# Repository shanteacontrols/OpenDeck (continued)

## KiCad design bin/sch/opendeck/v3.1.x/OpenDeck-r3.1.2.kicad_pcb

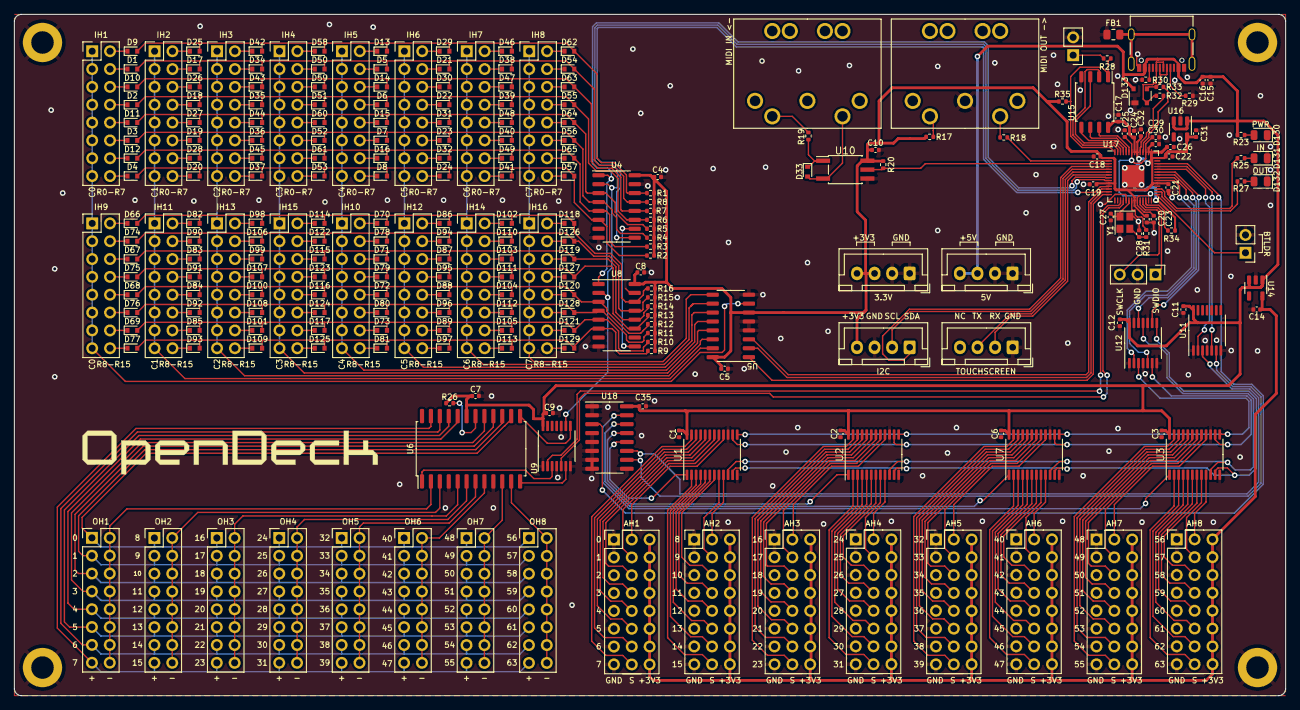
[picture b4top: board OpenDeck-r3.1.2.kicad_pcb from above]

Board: 2 copper layers, 181.0 x 97.0 mm, 262 parts (0 on the bottom side), 304 nets.

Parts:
AH1, AH2, AH3, AH4, AH5, AH6, AH7, AH8: 3x08
C1, C2, C3, C4, C5, C6, C7, C8, C9, C10, C11, C12, C16, C17, C18, C19, C20, C21, C22, C23, C24, C25, C26, C32, C35: 100n; C_0402_1005Metric
C14, C29, C30, C31: 1u; C_0402_1005Metric
C15: 10u; C_0402_1005Metric
C27, C28: 16p; C_0402_1005Metric
D1, D2, D3, D4, D5, D6, D7, D8, D9, D10, D11, D12, D13, D14, D15, D16, D17, D18, D19, D20, D21, D22, D23, D24, D25, D26, D27, D28, D29, D30, D31, D32, D33, D34, D35, D36, D37, D38, D39, D40, D41, D42, D43, D44, D45, D46, D47, D48, D49, D50, D51, D52, D53, D54, D55, D56, D57, D58, D59, D60, D61, D62, D63, D64, D65, D66, D67, D68, D69, D70, D71, D72, D73, D74, D75, D76, D77, D78, D79, D80, D81, D82, D83, D84, D85, D86, D87, D88, D89, D90, D91, D92, D93, D94, D95, D96, D97, D98, D99, D100, D101, D102, D103, D104, D105, D106, D107, D108, D109, D110, D111, D112, D113, D114, D115, D116, D117, D118, D119, D120, D121, D122, D123, D124, D125, D126, D127, D128, D129: 1N4148WT; D_SOD-523
D130: Red; LED_0805_2012Metric
D131: Green; LED_0805_2012Metric
D132: Blue; LED_0805_2012Metric
D133: PRTR5V0U2X; SOT-143
FB1: FerriteBead; R_0805_2012Metric
H1, H2, H3, H4: MountingHole_Pad; MountingHole_3.2mm_M3_DIN965_Pad
IH1, IH2, IH3, IH4, IH5, IH6, IH7, IH8, IH9, IH10, IH11, IH12, IH13, IH14, IH15, IH16: Conn_02x08_Top_Bottom; PinHeader_2x08_P2.54mm_Vertical
J1, J2: DIN-5; DIN5
J3, J6, J7, J8: Conn_01x04; JST_XH_B4B-XH-A_1x04_P2.50mm_Vertical
J5, J11: Conn_01x02; PinHeader_1x02_P2.54mm_Vertical
J9: TYPE-C-31-M-12
J10: Conn_01x03; PinHeader_1x03_P2.54mm_Vertical
OH1, OH2, OH3, OH4, OH5, OH6, OH7, OH8: Conn_02x08_Top_Bottom; PinHeader_2x08_P2.54mm_Vertical
R1, R2, R3, R4, R5, R6, R7, R8, R9, R10, R11, R12, R13, R14, R15, R16, R20: 4.7k; R_0402_1005Metric
R17: 33; R_0402_1005Metric
R18: 10; R_0402_1005Metric
R19: 220; R_0402_1005Metric
R23, R27, R28, R31: 1k; R_0402_1005Metric
R25: 680; R_0402_1005Metric
R26, R34, R35: 10k; R_0402_1005Metric
R29, R30: 5.1k; R_0402_1005Metric
R32, R33: 27; R_0402_1005Metric
U1, U2, U3, U7: 74HC4067; TSSOP-24_4.4x7.8mm_P0.65mm
U4, U8: 74HC165; SO-16_3.9x9.9mm_P1.27mm
U5: 74HC138; SO-16_3.9x9.9mm_P1.27mm
U6: MAX7219; SOIC-24W_7.5x15.4mm_P1.27mm
U9, U11, U12: 74HCT125; TSSOP-14_4.4x5mm_P0.65mm
U10: TLP2362; SO-5_4.4x3.6mm_P1.27mm
U14, U16: SPX3819M5; SOT-23-5
U15: W25Q128JVS; SOIC-8_5.23x5.23mm_P1.27mm
U17: RP2040; QFN-56-1EP_7x7mm_P0.4mm_EP3.2x3.2mm
U18: 4051; SOIC-16_3.9x9.9mm_P1.27mm
Y1: 12MHz; Crystal_SMD_2520-4Pin_2.5x2.0mm

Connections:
+1V1: C23.2, C25.2, C29.2, U17.23 (DVDD), U17.45 (VREG_VOUT), U17.50 (DVDD)
+3.3VADC: AH1.17, AH1.18, AH1.19, AH1.20, AH1.21, AH1.22, AH1.23, AH1.24, AH2.17, AH2.18, AH2.19, AH2.20, AH2.21, AH2.22, AH2.23, AH2.24, AH3.17, AH3.18, AH3.19, AH3.20, AH3.21, AH3.22, AH3.23, AH3.24, AH4.17, AH4.18, AH4.19, AH4.20, AH4.21, AH4.22, AH4.23, AH4.24, AH5.17, AH5.18, AH5.19, AH5.20, AH5.21, AH5.22, AH5.23, AH5.24, AH6.17, AH6.18, AH6.19, AH6.20, AH6.21, AH6.22, AH6.23, AH6.24, AH7.17, AH7.18, AH7.19, AH7.20, AH7.21, AH7.22, AH7.23, AH7.24, AH8.17, AH8.18, AH8.19, AH8.20, AH8.21, AH8.22, AH8.23, AH8.24, C14.2, U14.5 (OUT)
+3V3: C4.2, C5.2, C8.2, C10.2, C17.1, C18.1, C19.1, C20.1, C21.1, C22.1, C24.1, C26.1, C30.1, C31.2, C32.1, J6.4, J7.3, J7.4, R1.2, R2.2, R3.2, R4.2, R5.2, R6.2, R7.2, R8.2, R9.2, R10.2, R11.2, R12.2, R13.2, R14.2, R15.2, R16.2, R17.2, R20.1, R34.1, R35.1, U4.16 (VCC), U5.6 (E3), U5.16 (VCC), U8.16 (VCC), U10.6 (VCC), U15.8 (VCC), U16.5 (OUT), U17.1 (IOVDD), U17.10 (IOVDD), U17.22 (IOVDD), U17.33 (IOVDD), U17.42 (IOVDD), U17.43 (ADC_AVDD), U17.44 (VREG_VIN), U17.48 (USB_VDD), U17.49 (IOVDD)
+5V: C1.2, C2.2, C3.2, C6.2, C7.2, C9.2, C11.2, C12.2, C15.2, C16.2, C35.2, D133.4 (VCC), J8.3, J8.4, J9.A4/B9 (VBUS), J9.B4/A9 (VBUS), R23.1, R26.1, U1.24 (VCC), U2.24 (VCC), U3.24 (VCC), U6.19 (V+), U7.24 (VCC), U9.14 (VCC), U11.14 (VCC), U12.14 (VCC), U14.1 (IN), U14.3 (EN), U16.1 (IN), U16.3 (EN), U18.16 (VCC)
/Analog/MUX_COMMON_1: U1.1 (COM), U18.12 (Y3)
/Analog/MUX_COMMON_2: U2.1 (COM), U18.13 (Y0)
/Analog/MUX_COMMON_3: U7.1 (COM), U18.14 (Y1)
/Analog/MUX_COMMON_4: U3.1 (COM), U18.15 (Y2)
/Analog/MUX_S0_5V: U1.10 (S0), U2.10 (S0), U3.10 (S0), U7.10 (S0), U12.11
/Analog/MUX_S1_5V: U1.11 (S1), U2.11 (S1), U3.11 (S1), U7.11 (S1), U12.8
/Analog/MUX_S2_5V: U1.14 (S2), U2.14 (S2), U3.14 (S2), U7.14 (S2), U12.6
/Analog/MUX_S3_5V: U1.13 (S3), U2.13 (S3), U3.13 (S3), U7.13 (S3), U12.3
/Analog/Multiplexer 1/A_IN_0: AH2.9, U1.9 (Y0)
/Analog/Multiplexer 1/A_IN_1: AH2.10, U1.8 (Y1)
/Analog/Multiplexer 1/A_IN_2: AH2.11, U1.7 (Y2)
/Analog/Multiplexer 1/A_IN_3: AH2.12, U1.6 (Y3)
/Analog/Multiplexer 1/A_IN_4: AH2.13, U1.5 (Y4)
/Analog/Multiplexer 1/A_IN_5: AH2.14, U1.4 (Y5)
/Analog/Multiplexer 1/A_IN_6: AH2.15, U1.3 (Y6)
/Analog/Multiplexer 1/A_IN_7: AH2.16, U1.2 (Y7)
/Analog/Multiplexer 1/A_IN_8: AH1.16, U1.23 (Y8)
/Analog/Multiplexer 1/A_IN_9: AH1.15, U1.22 (Y9)
/Analog/Multiplexer 1/A_IN_10: AH1.14, U1.21 (Y10)
/Analog/Multiplexer 1/A_IN_11: AH1.13, U1.20 (Y11)
/Analog/Multiplexer 1/A_IN_12: AH1.12, U1.19 (Y12)
/Analog/Multiplexer 1/A_IN_13: AH1.11, U1.18 (Y13)
/Analog/Multiplexer 1/A_IN_14: AH1.10, U1.17 (Y14)
/Analog/Multiplexer 1/A_IN_15: AH1.9, U1.16 (Y15)
/Analog/Multiplexer 2/A_IN_0: AH4.9, U2.9 (Y0)
/Analog/Multiplexer 2/A_IN_1: AH4.10, U2.8 (Y1)
/Analog/Multiplexer 2/A_IN_2: AH4.11, U2.7 (Y2)
/Analog/Multiplexer 2/A_IN_3: AH4.12, U2.6 (Y3)
/Analog/Multiplexer 2/A_IN_4: AH4.13, U2.5 (Y4)
/Analog/Multiplexer 2/A_IN_5: AH4.14, U2.4 (Y5)
/Analog/Multiplexer 2/A_IN_6: AH4.15, U2.3 (Y6)
/Analog/Multiplexer 2/A_IN_7: AH4.16, U2.2 (Y7)
/Analog/Multiplexer 2/A_IN_8: AH3.16, U2.23 (Y8)
/Analog/Multiplexer 2/A_IN_9: AH3.15, U2.22 (Y9)
/Analog/Multiplexer 2/A_IN_10: AH3.14, U2.21 (Y10)
/Analog/Multiplexer 2/A_IN_11: AH3.13, U2.20 (Y11)
/Analog/Multiplexer 2/A_IN_12: AH3.12, U2.19 (Y12)
/Analog/Multiplexer 2/A_IN_13: AH3.11, U2.18 (Y13)
/Analog/Multiplexer 2/A_IN_14: AH3.10, U2.17 (Y14)
/Analog/Multiplexer 2/A_IN_15: AH3.9, U2.16 (Y15)
/Analog/Multiplexer 3/A_IN_0: AH6.9, U7.9 (Y0)
/Analog/Multiplexer 3/A_IN_1: AH6.10, U7.8 (Y1)
/Analog/Multiplexer 3/A_IN_2: AH6.11, U7.7 (Y2)
/Analog/Multiplexer 3/A_IN_3: AH6.12, U7.6 (Y3)
/Analog/Multiplexer 3/A_IN_4: AH6.13, U7.5 (Y4)
/Analog/Multiplexer 3/A_IN_5: AH6.14, U7.4 (Y5)
/Analog/Multiplexer 3/A_IN_6: AH6.15, U7.3 (Y6)
/Analog/Multiplexer 3/A_IN_7: AH6.16, U7.2 (Y7)
/Analog/Multiplexer 3/A_IN_8: AH5.16, U7.23 (Y8)
/Analog/Multiplexer 3/A_IN_9: AH5.15, U7.22 (Y9)
/Analog/Multiplexer 3/A_IN_10: AH5.14, U7.21 (Y10)
/Analog/Multiplexer 3/A_IN_11: AH5.13, U7.20 (Y11)
/Analog/Multiplexer 3/A_IN_12: AH5.12, U7.19 (Y12)
/Analog/Multiplexer 3/A_IN_13: AH5.11, U7.18 (Y13)
/Analog/Multiplexer 3/A_IN_14: AH5.10, U7.17 (Y14)
/Analog/Multiplexer 3/A_IN_15: AH5.9, U7.16 (Y15)
/Analog/Multiplexer 4/A_IN_0: AH8.9, U3.9 (Y0)
/Analog/Multiplexer 4/A_IN_1: AH8.10, U3.8 (Y1)
/Analog/Multiplexer 4/A_IN_2: AH8.11, U3.7 (Y2)
/Analog/Multiplexer 4/A_IN_3: AH8.12, U3.6 (Y3)
/Analog/Multiplexer 4/A_IN_4: AH8.13, U3.5 (Y4)
/Analog/Multiplexer 4/A_IN_5: AH8.14, U3.4 (Y5)
/Analog/Multiplexer 4/A_IN_6: AH8.15, U3.3 (Y6)
/Analog/Multiplexer 4/A_IN_7: AH8.16, U3.2 (Y7)
/Analog/Multiplexer 4/A_IN_8: AH7.16, U3.23 (Y8)
/Analog/Multiplexer 4/A_IN_9: AH7.15, U3.22 (Y9)
/Analog/Multiplexer 4/A_IN_10: AH7.14, U3.21 (Y10)
/Analog/Multiplexer 4/A_IN_11: AH7.13, U3.20 (Y11)
/Analog/Multiplexer 4/A_IN_12: AH7.12, U3.19 (Y12)
/Analog/Multiplexer 4/A_IN_13: AH7.11, U3.18 (Y13)
/Analog/Multiplexer 4/A_IN_14: AH7.10, U3.17 (Y14)
/Analog/Multiplexer 4/A_IN_15: AH7.9, U3.16 (Y15)
/BTLDR: J5.1, U17.29 (GPIO18)
/Buttons/BC_0: IH1.1, IH1.3, IH1.5, IH1.7, IH1.9, IH1.11, IH1.13, IH1.15, IH9.1, IH9.3, IH9.5, IH9.7, IH9.9, IH9.11, IH9.13, IH9.15, U5.7 (~Y7)
/Buttons/BC_1: IH2.1, IH2.3, IH2.5, IH2.7, IH2.9, IH2.11, IH2.13, IH2.15, IH11.1, IH11.3, IH11.5, IH11.7, IH11.9, IH11.11, IH11.13, IH11.15, U5.15 (~Y0)
/Buttons/BC_2: IH3.1, IH3.3, IH3.5, IH3.7, IH3.9, IH3.11, IH3.13, IH3.15, IH13.1, IH13.3, IH13.5, IH13.7, IH13.9, IH13.11, IH13.13, IH13.15, U5.14 (~Y1)
/Buttons/BC_3: IH4.1, IH4.3, IH4.5, IH4.7, IH4.9, IH4.11, IH4.13, IH4.15, IH15.1, IH15.3, IH15.5, IH15.7, IH15.9, IH15.11, IH15.13, IH15.15, U5.13 (~Y2)
/Buttons/BC_4: IH5.1, IH5.3, IH5.5, IH5.7, IH5.9, IH5.11, IH5.13, IH5.15, IH10.1, IH10.3, IH10.5, IH10.7, IH10.9, IH10.11, IH10.13, IH10.15, U5.12 (~Y3)
/Buttons/BC_5: IH6.1, IH6.3, IH6.5, IH6.7, IH6.9, IH6.11, IH6.13, IH6.15, IH12.1, IH12.3, IH12.5, IH12.7, IH12.9, IH12.11, IH12.13, IH12.15, U5.11 (~Y4)
/Buttons/BC_6: IH7.1, IH7.3, IH7.5, IH7.7, IH7.9, IH7.11, IH7.13, IH7.15, IH14.1, IH14.3, IH14.5, IH14.7, IH14.9, IH14.11, IH14.13, IH14.15, U5.10 (~Y5)
/Buttons/BC_7: IH8.1, IH8.3, IH8.5, IH8.7, IH8.9, IH8.11, IH8.13, IH8.15, IH16.1, IH16.3, IH16.5, IH16.7, IH16.9, IH16.11, IH16.13, IH16.15, U5.9 (~Y6)
/Buttons/Rows 0-7/BR_0: D9.2 (A), D13.2 (A), D25.2 (A), D29.2 (A), D42.2 (A), D46.2 (A), D58.2 (A), D62.2 (A), R1.1, U4.14 (D3)
/Buttons/Rows 0-7/BR_1: D1.2 (A), D5.2 (A), D17.2 (A), D21.2 (A), D34.2 (A), D38.2 (A), D50.2 (A), D54.2 (A), R8.1, U4.13 (D2)
/Buttons/Rows 0-7/BR_2: D10.2 (A), D14.2 (A), D26.2 (A), D30.2 (A), D43.2 (A), D47.2 (A), D59.2 (A), D63.2 (A), R7.1, U4.12 (D1)
/Buttons/Rows 0-7/BR_3: D2.2 (A), D6.2 (A), D18.2 (A), D22.2 (A), D35.2 (A), D39.2 (A), D51.2 (A), D55.2 (A), R6.1, U4.11 (D0)
/Buttons/Rows 0-7/BR_4: D11.2 (A), D15.2 (A), D27.2 (A), D31.2 (A), D44.2 (A), D48.2 (A), D60.2 (A), D64.2 (A), R5.1, U4.3 (D4)
/Buttons/Rows 0-7/BR_5: D3.2 (A), D7.2 (A), D19.2 (A), D23.2 (A), D36.2 (A), D40.2 (A), D52.2 (A), D56.2 (A), R4.1, U4.4 (D5)
/Buttons/Rows 0-7/BR_6: D12.2 (A), D16.2 (A), D28.2 (A), D32.2 (A), D45.2 (A), D49.2 (A), D61.2 (A), D65.2 (A), R3.1, U4.5 (D6)
/Buttons/Rows 0-7/BR_7: D4.2 (A), D8.2 (A), D20.2 (A), D24.2 (A), D37.2 (A), D41.2 (A), D53.2 (A), D57.2 (A), R2.1, U4.6 (D7)
/Buttons/Rows 8-15/BR_0: D66.2 (A), D70.2 (A), D82.2 (A), D86.2 (A), D98.2 (A), D102.2 (A), D114.2 (A), D118.2 (A), R16.1, U8.14 (D3)
/Buttons/Rows 8-15/BR_1: D74.2 (A), D78.2 (A), D90.2 (A), D94.2 (A), D106.2 (A), D110.2 (A), D122.2 (A), D126.2 (A), R15.1, U8.13 (D2)
/Buttons/Rows 8-15/BR_2: D67.2 (A), D71.2 (A), D83.2 (A), D87.2 (A), D99.2 (A), D103.2 (A), D115.2 (A), D119.2 (A), R14.1, U8.12 (D1)
/Buttons/Rows 8-15/BR_3: D75.2 (A), D79.2 (A), D91.2 (A), D95.2 (A), D107.2 (A), D111.2 (A), D123.2 (A), D127.2 (A), R13.1, U8.11 (D0)
/Buttons/Rows 8-15/BR_4: D68.2 (A), D72.2 (A), D84.2 (A), D88.2 (A), D100.2 (A), D104.2 (A), D116.2 (A), D120.2 (A), R12.1, U8.3 (D4)
/Buttons/Rows 8-15/BR_5: D76.2 (A), D80.2 (A), D92.2 (A), D96.2 (A), D108.2 (A), D112.2 (A), D124.2 (A), D128.2 (A), R11.1, U8.4 (D5)
/Buttons/Rows 8-15/BR_6: D69.2 (A), D73.2 (A), D85.2 (A), D89.2 (A), D101.2 (A), D105.2 (A), D117.2 (A), D121.2 (A), R10.1, U8.5 (D6)
/Buttons/Rows 8-15/BR_7: D77.2 (A), D81.2 (A), D93.2 (A), D97.2 (A), D109.2 (A), D113.2 (A), D125.2 (A), D129.2 (A), R9.1, U8.6 (D7)
/Buttons/SR_DAISY_OUT_1: U4.10 (DS), U8.9 (Q7)
/DEC_DI_A0: U5.1 (A0), U17.14 (GPIO11)
/DEC_DI_A1: U5.2 (A1), U17.13 (GPIO10)
/DEC_DI_A2: U5.3 (A2), U17.12 (GPIO9)
/LEDs/LED_COLUMN_1: OH1.2, OH1.4, OH1.6, OH1.8, OH1.10, OH1.12, OH1.14, OH1.16, U6.2 (DIG_0)
/LEDs/LED_COLUMN_2: OH2.2, OH2.4, OH2.6, OH2.8, OH2.10, OH2.12, OH2.14, OH2.16, U6.3 (DIG_4)
/LEDs/LED_COLUMN_3: OH3.2, OH3.4, OH3.6, OH3.8, OH3.10, OH3.12, OH3.14, OH3.16, U6.5 (DIG_6)
/LEDs/LED_COLUMN_4: OH4.2, OH4.4, OH4.6, OH4.8, OH4.10, OH4.12, OH4.14, OH4.16, U6.6 (DIG_2)
/LEDs/LED_COLUMN_5: OH5.2, OH5.4, OH5.6, OH5.8, OH5.10, OH5.12, OH5.14, OH5.16, U6.7 (DIG_3)
/LEDs/LED_COLUMN_6: OH6.2, OH6.4, OH6.6, OH6.8, OH6.10, OH6.12, OH6.14, OH6.16, U6.8 (DIG_7)
/LEDs/LED_COLUMN_7: OH7.2, OH7.4, OH7.6, OH7.8, OH7.10, OH7.12, OH7.14, OH7.16, U6.10 (DIG_5)
/LEDs/LED_COLUMN_8: OH8.2, OH8.4, OH8.6, OH8.8, OH8.10, OH8.12, OH8.14, OH8.16, U6.11 (DIG_1)
/LEDs/LED_ROW_1: OH1.1, OH2.1, OH3.1, OH4.1, OH5.1, OH6.1, OH7.1, OH8.1, U6.14 (SEG_A)
/LEDs/LED_ROW_2: OH1.3, OH2.3, OH3.3, OH4.3, OH5.3, OH6.3, OH7.3, OH8.3, U6.15 (SEG_F)
/LEDs/LED_ROW_3: OH1.5, OH2.5, OH3.5, OH4.5, OH5.5, OH6.5, OH7.5, OH8.5, U6.16 (SEG_B)
/LEDs/LED_ROW_4: OH1.7, OH2.7, OH3.7, OH4.7, OH5.7, OH6.7, OH7.7, OH8.7, U6.17 (SEG_G)
/LEDs/LED_ROW_5: OH1.9, OH2.9, OH3.9, OH4.9, OH5.9, OH6.9, OH7.9, OH8.9, U6.20 (SEG_C)
/LEDs/LED_ROW_6: OH1.11, OH2.11, OH3.11, OH4.11, OH5.11, OH6.11, OH7.11, OH8.11, U6.21 (SEG_E)
/LEDs/LED_ROW_7: OH1.13, OH2.13, OH3.13, OH4.13, OH5.13, OH6.13, OH7.13, OH8.13, U6.22 (SEG_DP)
/LEDs/LED_ROW_8: OH1.15, OH2.15, OH3.15, OH4.15, OH5.15, OH6.15, OH7.15, OH8.15, U6.23 (SEG_D)
/MAX7219_DIN: U9.2 (1A), U17.17 (GPIO14)
/MAX7219_LOAD: U9.5 (2A), U17.18 (GPIO15)
/MIDI_RX: R20.2, U10.5 (VO), U17.3 (GPIO1)
/MIDI_TX: R18.2, U17.2 (GPIO0)
/MUX_COMMON: U17.40 (GPIO28_ADC2), U18.3 (COM)
/MUX_S0: U12.12, U17.36 (GPIO24)
/MUX_S1: U12.9, U17.37 (GPIO25)
/MUX_S2: U12.5, U17.35 (GPIO23)
/MUX_S3: U12.2, U17.34 (GPIO22)
/MUX_SEL0: U11.2, U17.38 (GPIO26_ADC0)
/MUX_SEL1: U11.5, U17.39 (GPIO27_ADC1)
/QSPI_CLK: U15.6 (CLK), U17.52 (QSPI_SCLK)
/QSPI_CS: R28.1, R35.2, U15.1 (~CS), U17.56 (QSPI_SS)
/QSPI_IO0: U15.5 (IO0), U17.53 (QSPI_SD0)
/QSPI_IO1: U15.2 (IO1), U17.55 (QSPI_SD1)
/QSPI_IO2: U15.3 (IO2), U17.54 (QSPI_SD2)
/QSPI_IO3: U15.7 (IO3), U17.51 (QSPI_SD3)
/SCL: J6.2, U17.5 (GPIO3)
/SDA: J6.1, U17.4 (GPIO2)
/SPI_CLK: U4.2 (CP), U8.2 (CP), U9.9 (3A), U17.9 (GPIO7)
/SR_IN_DATA: U4.9 (Q7), U17.11 (GPIO8)
/SR_IN_LATCH: U4.1 (~PL), U8.1 (~PL), U17.8 (GPIO6)
/SWCLK: J10.3, U17.24 (SWCLK)
/SWD: J10.1, U17.25 (SWD)
/TRAFFIC_IN: R25.1, U17.31 (GPIO20)
/TRAFFIC_OUT: R27.1, U17.30 (GPIO19)
/TSCREEN_RX: J3.2, U17.7 (GPIO5)
/TSCREEN_TX: J3.3, U17.6 (GPIO4)
/USB_DM: D133.3 (I/O2), J9.A7 (DN1), J9.B7 (DN2), R33.1
/USB_DP: D133.2 (I/O1), J9.A6 (DP1), J9.B6 (DP2), R32.1
/~USB_BOOT: J11.1, R28.2
GND: AH1.1, AH1.2, AH1.3, AH1.4, AH1.5, AH1.6, AH1.7, AH1.8, AH2.1, AH2.2, AH2.3, AH2.4, AH2.5, AH2.6, AH2.7, AH2.8, AH3.1, AH3.2, AH3.3, AH3.4, AH3.5, AH3.6, AH3.7, AH3.8, AH4.1, AH4.2, AH4.3, AH4.4, AH4.5, AH4.6, AH4.7, AH4.8, AH5.1, AH5.2, AH5.3, AH5.4, AH5.5, AH5.6, AH5.7, AH5.8, AH6.1, AH6.2, AH6.3, AH6.4, AH6.5, AH6.6, AH6.7, AH6.8, AH7.1, AH7.2, AH7.3, AH7.4, AH7.5, AH7.6, AH7.7, AH7.8, AH8.1, AH8.2, AH8.3, AH8.4, AH8.5, AH8.6, AH8.7, AH8.8, C1.1, C2.1, C3.1, C4.1, C5.1, C6.1, C7.1, C8.1, C9.1, C10.1, C11.1, C12.1, C14.1, C15.1, C16.1, C17.2, C18.2, C19.2, C20.2, C21.2, C22.2, C23.1, C24.2, C25.1, C26.2, C27.2, C28.1, C29.1, C30.2, C31.1, C32.2, C35.1, D130.1 (K), D131.1 (K), D132.1 (K), D133.1 (GND), FB1.1, H1.1, H2.1, H3.1, H4.1, J1.2, J3.1, J5.2, J6.3, J7.1, J7.2, J8.1, J8.2, J9.A1/B12 (GND), J9.B1/A12 (GND), J10.2, J11.2, R29.2, R30.2, U1.12 (GND), U1.15 (~E), U2.12 (GND), U2.15 (~E), U3.12 (GND), U3.15 (~E), U4.8 (GND), U4.15 (~CE), U5.4 (~E1), U5.5 (~E2), U5.8 (GND), U6.4 (GND), U6.9 (GND), U7.12 (GND), U7.15 (~E), U8.8 (GND), U8.15 (~CE), U9.1 (1~OE), U9.4 (2~OE), U9.7 (GND), U9.10 (3~OE), U10.4 (GND), U11.1, U11.4, U11.7 (GND), U12.1, U12.4, U12.7 (GND), U12.10, U12.13, U14.2 (GND), U15.4 (GND), U16.2 (GND), U17.19 (TESTEN), U17.57 (GND), U18.1 (Y4), U18.2 (Y6), U18.4 (Y7), U18.5 (Y5), U18.6 (~E), U18.7 (VEE), U18.8 (GND), U18.9 (S2), Y1.2, Y1.4
unnamed: C28.2, R31.1, Y1.3
unnamed: D1.1 (K), IH1.4
unnamed: D2.1 (K), IH1.8
unnamed: D3.1 (K), IH1.12
unnamed: D4.1 (K), IH1.16
unnamed: D5.1 (K), IH5.4
unnamed: D6.1 (K), IH5.8
unnamed: D7.1 (K), IH5.12
unnamed: D8.1 (K), IH5.16
unnamed: D9.1 (K), IH1.2
unnamed: D10.1 (K), IH1.6
unnamed: D11.1 (K), IH1.10
unnamed: D12.1 (K), IH1.14
unnamed: D13.1 (K), IH5.2
unnamed: D14.1 (K), IH5.6
unnamed: D15.1 (K), IH5.10
unnamed: D16.1 (K), IH5.14
unnamed: D17.1 (K), IH2.4
unnamed: D18.1 (K), IH2.8
unnamed: D19.1 (K), IH2.12
unnamed: D20.1 (K), IH2.16
unnamed: D21.1 (K), IH6.4
unnamed: D22.1 (K), IH6.8
unnamed: D23.1 (K), IH6.12
unnamed: D24.1 (K), IH6.16
unnamed: D25.1 (K), IH2.2
unnamed: D26.1 (K), IH2.6
unnamed: D27.1 (K), IH2.10
unnamed: D28.1 (K), IH2.14
unnamed: D29.1 (K), IH6.2
unnamed: D30.1 (K), IH6.6
unnamed: D31.1 (K), IH6.10
unnamed: D32.1 (K), IH6.14
unnamed: D33.2 (A), J2.5, U10.3 (C)
unnamed: D33.1 (K), R19.2, U10.1 (A)
unnamed: D34.1 (K), IH3.4
unnamed: D35.1 (K), IH3.8
unnamed: D36.1 (K), IH3.12
unnamed: D37.1 (K), IH3.16
unnamed: D38.1 (K), IH7.4
unnamed: D39.1 (K), IH7.8
unnamed: D40.1 (K), IH7.12
unnamed: D41.1 (K), IH7.16
unnamed: D42.1 (K), IH3.2
unnamed: D43.1 (K), IH3.6
unnamed: D44.1 (K), IH3.10
unnamed: D45.1 (K), IH3.14
unnamed: D46.1 (K), IH7.2
unnamed: D47.1 (K), IH7.6
unnamed: D48.1 (K), IH7.10
unnamed: D49.1 (K), IH7.14
unnamed: D50.1 (K), IH4.4
unnamed: D51.1 (K), IH4.8
unnamed: D52.1 (K), IH4.12
unnamed: D53.1 (K), IH4.16
unnamed: D54.1 (K), IH8.4
unnamed: D55.1 (K), IH8.8
unnamed: D56.1 (K), IH8.12
unnamed: D57.1 (K), IH8.16
unnamed: D58.1 (K), IH4.2
unnamed: D59.1 (K), IH4.6
unnamed: D60.1 (K), IH4.10
unnamed: D61.1 (K), IH4.14
unnamed: D62.1 (K), IH8.2
unnamed: D63.1 (K), IH8.6
unnamed: D64.1 (K), IH8.10
unnamed: D65.1 (K), IH8.14
unnamed: D66.1 (K), IH9.2
unnamed: D67.1 (K), IH9.6
unnamed: D68.1 (K), IH9.10
unnamed: D69.1 (K), IH9.14
unnamed: D70.1 (K), IH10.2
unnamed: D71.1 (K), IH10.6
unnamed: D72.1 (K), IH10.10
unnamed: D73.1 (K), IH10.14
unnamed: D74.1 (K), IH9.4
unnamed: D75.1 (K), IH9.8
unnamed: D76.1 (K), IH9.12
unnamed: D77.1 (K), IH9.16
unnamed: D78.1 (K), IH10.4
unnamed: D79.1 (K), IH10.8
unnamed: D80.1 (K), IH10.12
unnamed: D81.1 (K), IH10.16
unnamed: D82.1 (K), IH11.2
unnamed: D83.1 (K), IH11.6
unnamed: D84.1 (K), IH11.10
unnamed: D85.1 (K), IH11.14
unnamed: D86.1 (K), IH12.2
unnamed: D87.1 (K), IH12.6
unnamed: D88.1 (K), IH12.10
unnamed: D89.1 (K), IH12.14
unnamed: D90.1 (K), IH11.4
unnamed: D91.1 (K), IH11.8
unnamed: D92.1 (K), IH11.12
unnamed: D93.1 (K), IH11.16
unnamed: D94.1 (K), IH12.4
unnamed: D95.1 (K), IH12.8
unnamed: D96.1 (K), IH12.12
unnamed: D97.1 (K), IH12.16
unnamed: D98.1 (K), IH13.2
unnamed: D99.1 (K), IH13.6
unnamed: D100.1 (K), IH13.10
unnamed: D101.1 (K), IH13.14
unnamed: D102.1 (K), IH14.2
unnamed: D103.1 (K), IH14.6
unnamed: D104.1 (K), IH14.10
unnamed: D105.1 (K), IH14.14
unnamed: D106.1 (K), IH13.4
unnamed: D107.1 (K), IH13.8
unnamed: D108.1 (K), IH13.12
unnamed: D109.1 (K), IH13.16
unnamed: D110.1 (K), IH14.4
unnamed: D111.1 (K), IH14.8
unnamed: D112.1 (K), IH14.12
unnamed: D113.1 (K), IH14.16
unnamed: D114.1 (K), IH15.2
unnamed: D115.1 (K), IH15.6
unnamed: D116.1 (K), IH15.10
unnamed: D117.1 (K), IH15.14
unnamed: D118.1 (K), IH16.2
unnamed: D119.1 (K), IH16.6
unnamed: D120.1 (K), IH16.10
unnamed: D121.1 (K), IH16.14
unnamed: D122.1 (K), IH15.4
unnamed: D123.1 (K), IH15.8
unnamed: D124.1 (K), IH15.12
unnamed: D125.1 (K), IH15.16
unnamed: D126.1 (K), IH16.4
unnamed: D127.1 (K), IH16.8
unnamed: D128.1 (K), IH16.12
unnamed: D129.1 (K), IH16.16
unnamed: D130.2 (A), R23.2
unnamed: D131.2 (A), R25.2
unnamed: D132.2 (A), R27.2
unnamed: FB1.2, J9.S1 (SHIELD), J9.S2 (SHIELD), J9.S3 (SHIELD), J9.S4 (SHIELD)
unnamed: J1.4, R17.1
unnamed: J1.5, R18.1
unnamed: J2.4, R19.1
unnamed: J9.A5 (CC1), R29.1
unnamed: J9.B5 (CC2), R30.1
unnamed: U6.13 (CLK), U9.8 (3Y)
unnamed: U6.1 (DIN), U9.3 (1Y)
unnamed: R26.2, U6.18 (ISET)
unnamed: U6.12 (LOAD), U9.6 (2Y)
unnamed: R34.2, U17.26 (RUN)
unnamed: R33.2, U17.46 (USB_DM)
unnamed: R32.2, U17.47 (USB_DP)
unnamed: C27.1, U17.20 (XIN), Y1.1
unnamed: R31.2, U17.21 (XOUT)
unnamed: U11.3, U18.11 (S0)
unnamed: U11.6, U18.10 (S1)

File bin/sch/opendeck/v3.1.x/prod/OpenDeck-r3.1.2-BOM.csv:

Comment,Designator,Footprint,LCSC
"3x08","AH1,AH2,AH3,AH4,AH5,AH6,AH7,AH8","igor_footprint_lib:3x08",""
"10u","C15","Capacitor_SMD:C_0402_1005Metric","C15525"
"100n","C1,C2,C3,C4,C5,C6,C7,C8,C9,C10,C11,C12,C16,C17,C18,C19,C20,C21,C22,C23,C24,C25,C26,C32,C35","Capacitor_SMD:C_0402_1005Metric","C1525"
"16p","C27,C28","Capacitor_SMD:C_0402_1005Metric","C161307"
"1u","C14,C29,C30,C31","Capacitor_SMD:C_0402_1005Metric","C52923"
"1N4148WT","D1,D2,D3,D4,D5,D6,D7,D8,D9,D10,D11,D12,D13,D14,D15,D16,D17,D18,D19,D20,D21,D22,D23,D24,D25,D26,D27,D28,D29,D30,D31,D32,D33,D34,D35,D36,D37,D38,D39,D40,D41,D42,D43,D44,D45,D46,D47,D48,D49,D50,D51,D52,D53,D54,D55,D56,D57,D58,D59,D60,D61,D62,D63,D64,D65,D66,D67,D68,D69,D70,D71,D72,D73,D74,D75,D76,D77,D78,D79,D80,D81,D82,D83,D84,D85,D86,D87,D88,D89,D90,D91,D92,D93,D94,D95,D96,D97,D98,D99,D100,D101,D102,D103,D104,D105,D106,D107,D108,D109,D110,D111,D112,D113,D114,D115,D116,D117,D118,D119,D120,D121,D122,D123,D124,D125,D126,D127,D128,D129","Diode_SMD:D_SOD-523","C232841"
"Red","D130","LED_SMD:LED_0805_2012Metric","C84256"
"Green","D131","LED_SMD:LED_0805_2012Metric","C142303"
"Blue","D132","LED_SMD:LED_0805_2012Metric","C84259"
"PRTR5V0U2X","D133","Package_TO_SOT_SMD:SOT-143","C2827688"
"FerriteBead","FB1","Resistor_SMD:R_0805_2012Metric","C85840"
"MountingHole_Pad","H1,H2,H3,H4","MountingHole:MountingHole_3.2mm_M3_DIN965_Pad",""
"Conn_02x08_Top_Bottom","IH1,OH1,IH2,OH2,IH3,OH3,IH4,OH4,IH5,OH5,IH6,OH6,IH7,OH7,IH8,OH8,IH9,IH10,IH11,IH12,IH13,IH14,IH15,IH16","Connector_PinHeader_2.54mm:PinHeader_2x08_P2.54mm_Vertical",""
"DIN-5","J1,J2","igor_footprint_lib:DIN5",""
"Conn_01x03","J10","Connector_PinHeader_2.54mm:PinHeader_1x03_P2.54mm_Vertical",""
"Conn_01x04","J3,J6,J7,J8","Connector_JST:JST_XH_B4B-XH-A_1x04_P2.50mm_Vertical",""
"Conn_01x02","J5,J11","Connector_PinHeader_2.54mm:PinHeader_1x02_P2.54mm_Vertical",""
"TYPE-C-31-M-12","J9","Igor:TYPE-C-31-M-12","C165948"
"4.7k","R1,R2,R3,R4,R5,R6,R7,R8,R9,R10,R11,R12,R13,R14,R15,R16,R20","Resistor_SMD:R_0402_1005Metric","C25900"
"33","R17","Resistor_SMD:R_0402_1005Metric","C25105"
"10","R18","Resistor_SMD:R_0402_1005Metric","C25077"
"220","R19","Resistor_SMD:R_0402_1005Metric","C25091"
"680","R25","Resistor_SMD:R_0402_1005Metric","C25130"
"1k","R23,R27,R28,R31","Resistor_SMD:R_0402_1005Metric","C11702"
"5.1k","R29,R30","Resistor_SMD:R_0402_1005Metric","C25905"
"27","R32,R33","Resistor_SMD:R_0402_1005Metric","C25100"
"10k","R26,R34,R35","Resistor_SMD:R_0402_1005Metric","C25744"
"74HC4067","U1,U2,U3,U7","Package_SO:TSSOP-24_4.4x7.8mm_P0.65mm","C179326"
"TLP2362","U10","Package_SO:SO-5_4.4x3.6mm_P1.27mm","C37658"
"W25Q128JVS","U15","Package_SO:SOIC-8_5.23x5.23mm_P1.27mm","C97521"
"SPX3819M5","U14,U16","Package_TO_SOT_SMD:SOT-23-5","C9055"
"RP2040","U17","Package_DFN_QFN:QFN-56-1EP_7x7mm_P0.4mm_EP3.2x3.2mm","C2040"
"4051","U18","Package_SO:SOIC-16_3.9x9.9mm_P1.27mm","C9386"
"74HC165","U4,U8","Package_SO:SO-16_3.9x9.9mm_P1.27mm","C5613"
"74HC138","U5","Package_SO:SO-16_3.9x9.9mm_P1.27mm","C6818"
"MAX7219","U6","Package_SO:SOIC-24W_7.5x15.4mm_P1.27mm","C9964"
"74HCT125","U9,U11,U12","Package_SO:TSSOP-14_4.4x5mm_P0.65mm","C36365"
"12MHz","Y1","Crystal:Crystal_SMD_2520-4Pin_2.5x2.0mm","C254355"

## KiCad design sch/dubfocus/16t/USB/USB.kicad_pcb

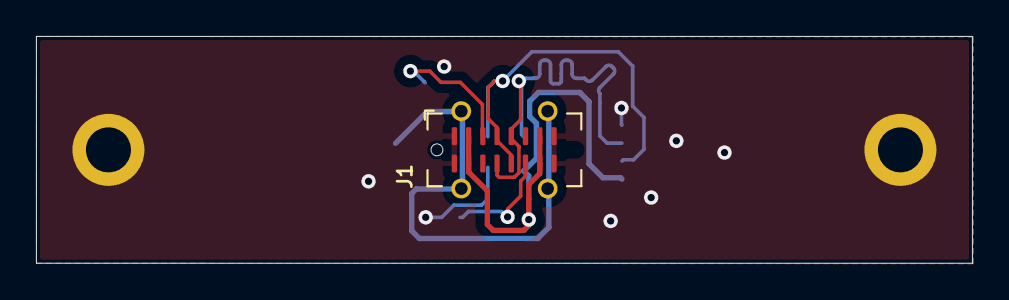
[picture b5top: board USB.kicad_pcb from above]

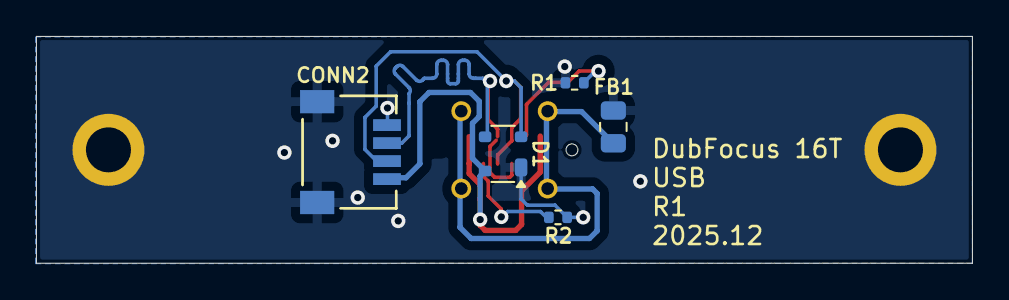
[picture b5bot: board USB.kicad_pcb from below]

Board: 2 copper layers, 52.0 x 12.6 mm, 8 parts (5 on the bottom side), 7 nets.

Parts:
CONN2: Conn_01x04; CONN_SM04B-SRSS-TB_JST
D1: PRTR5V0U2X; SOT-143
FB1: FerriteBead; R_0805_2012Metric
H1, H2: MountingHole_Pad; MountingHole_2.5mm_Pad
J1: USB_C_Receptacle_USB2.0_16P; USB_C_Receptacle_G-Switch_GT-USB-7051x
R1, R2: 5.1k; R_0402_1005Metric

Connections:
+5V: CONN2.4, D1.4 (VCC), J1.A4 (VBUS), J1.A9 (VBUS), J1.B4 (VBUS), J1.B9 (VBUS)
/SHIELD: FB1.2, J1.S1 (SHIELD)
/USB_DM: CONN2.2, D1.3 (I/O2), J1.A7 (D-), J1.B7 (D-)
/USB_DP: CONN2.3, D1.2 (I/O1), J1.A6 (D+), J1.B6 (D+)
GND: CONN2.1, CONN2.S1, CONN2.S2, D1.1 (GND), FB1.1, H1.1, H2.1, J1.A1 (GND), J1.A12 (GND), J1.B1 (GND), J1.B12 (GND), R1.2, R2.2
unnamed: J1.A5 (CC1), R1.1
unnamed: J1.B5 (CC2), R2.1

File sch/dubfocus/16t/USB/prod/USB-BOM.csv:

Comment,Designator,Footprint,LCSC
"Conn_01x04","CONN2","Igor:CONN_SM04B-SRSS-TB_JST","C160404"
"PRTR5V0U2X","D1","Package_TO_SOT_SMD:SOT-143","C2827688"
"FerriteBead","FB1","Resistor_SMD:R_0805_2012Metric","C85840"
"USB_C_Receptacle_USB2.0_16P","J1","Connector_USB:USB_C_Receptacle_G-Switch_GT-USB-7051x","C2843970"
"5.1k","R1,R2","Resistor_SMD:R_0402_1005Metric","C25905"

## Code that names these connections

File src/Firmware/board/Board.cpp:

/*
    OpenDeck MIDI platform firmware
    Copyright (C) 2015, 2016 Igor Petrovic

    This program is free software: you can redistribute it and/or modify
    it under the terms of the GNU General Public License as published by
    the Free Software Foundation, either version 3 of the License, or
    (at your option) any later version.

    This program is distributed in the hope that it will be useful,
    but WITHOUT ANY WARRANTY; without even the implied warranty of
    MERCHANTABILITY or FITNESS FOR A PARTICULAR PURPOSE.  See the
    GNU General Public License for more details.

    You should have received a copy of the GNU General Public License
    along with this program.  If not, see <http://www.gnu.org/licenses/>.
*/

#include "Board.h"
#include <util/delay.h>
#include <avr/cpufunc.h>
#include <avr/wdt.h>
#include <avr/eeprom.h>

Board::Board()
{
    //default constructor
}

void Board::init()
{
    cli();
    //disable watchdog
    MCUSR &= ~(1 << WDRF);
    wdt_disable();
    initPins();
    initAnalog();
    initEncoders();

    _delay_ms(5);

    configureTimers();

    //enable global interrupts
    sei();
}

void Board::initPins()
{
    //configure input matrix
    //shift register
    setInput(SR_DIN_PORT, SR_DIN_PIN);
    setOutput(SR_CLK_PORT, SR_CLK_PIN);
    setOutput(SR_LATCH_PORT, SR_LATCH_PIN);

    //decoder
    setOutput(DEC_DM_A0_PORT, DEC_DM_A0_PIN);
    setOutput(DEC_DM_A1_PORT, DEC_DM_A1_PIN);
    setOutput(DEC_DM_A1_PORT, DEC_DM_A2_PIN);

    //configure led matrix
    //rows

    setHigh(LED_ROW_1_PORT, LED_ROW_1_PIN);
    setHigh(LED_ROW_2_PORT, LED_ROW_2_PIN);
    setHigh(LED_ROW_3_PORT, LED_ROW_3_PIN);
    setHigh(LED_ROW_4_PORT, LED_ROW_4_PIN);
    setHigh(LED_ROW_5_PORT, LED_ROW_5_PIN);
    setHigh(LED_ROW_6_PORT, LED_ROW_6_PIN);

    setOutput(LED_ROW_1_PORT, LED_ROW_1_PIN);
    setOutput(LED_ROW_2_PORT, LED_ROW_2_PIN);
    setOutput(LED_ROW_3_PORT, LED_ROW_3_PIN);
    setOutput(LED_ROW_4_PORT, LED_ROW_4_PIN);
    setOutput(LED_ROW_5_PORT, LED_ROW_5_PIN);
    setOutput(LED_ROW_6_PORT, LED_ROW_6_PIN);

    //decoder
    setOutput(DEC_LM_A0_PORT, DEC_LM_A0_PIN);
    setOutput(DEC_LM_A1_PORT, DEC_LM_A1_PIN);
    setOutput(DEC_LM_A2_PORT, DEC_LM_A2_PIN);

    //configure analog
    //select pins
    setOutput(MUX_S0_PORT, MUX_S0_PIN);
    setOutput(MUX_S1_PORT, MUX_S1_PIN);
    setOutput(MUX_S2_PORT, MUX_S2_PIN);
    setOutput(MUX_S3_PORT, MUX_S3_PIN);

    //mux inputs
    setInput(MUX_1_IN_PORT, MUX_1_IN_PIN);
    setInput(MUX_2_IN_PORT, MUX_2_IN_PIN);

    //bootloader led
    setOutput(BTLDR_LED_PORT, BTLDR_LED_PIN);
}

void Board::configureTimers()
{
    //clear timer0 conf
    TCCR0A = 0;
    TCCR0B = 0;
    TIMSK0 = 0;

    //clear timer1 conf
    TCCR1A = 0;
    TCCR1B = 0;

    //clear timer3 conf
    TCCR3A = 0;
    TCCR3B = 0;

    //clear timer4 conf
    TCCR4A = 0;
    TCCR4B = 0;
    TCCR4C = 0;
    TCCR4D = 0;
    TCCR4E = 0;

    //set timer1, timer3 and timer4 to phase correct pwm mode
    //timer 1
    TCCR1A |= (1<<WGM10);           //phase correct PWM
    TCCR1B |= (1<<CS10);            //prescaler 1
    //timer 3
    TCCR3A |= (1<<WGM30);           //phase correct PWM
    TCCR3B |= (1<<CS30);            //prescaler 1
    //timer 4
    TCCR4A |= (1<<PWM4A);           //Pulse Width Modulator A Enable
    TCCR4B |= (1<<CS40);            //prescaler 1
    TCCR4C |= (1<<PWM4D);           //Pulse Width Modulator D Enable
    TCCR4D |= (1<<WGM40);           //phase correct PWM

    //set timer0 to ctc, used for millis/led matrix
    TCCR0A |= (1<<WGM01);           //CTC mode
    TCCR0B |= (1<<CS01)|(1<<CS00);  //prescaler 64
    OCR0A = 124;                    //500uS
    TIMSK0 |= (1<<OCIE0A);          //compare match interrupt
}

Board board;

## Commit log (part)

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2023-05-30 tests/bootloader: don't use internal board api
2023-05-31 clang_tidy_wrapper.sh: use consistent spacing
2023-05-31 vscode: don't hide build dir and compile_commands
2023-05-31 dockerfile: use clang from ubuntu repos
2023-06-01 scripts/dev.sh: always pull the latest image
2023-06-01 dockerfile: fixup comments
2023-06-01 misc: linting
2023-06-04 rewrite the build system in cmake
2023-06-04 tests: guard flash functions with ifdef
2023-06-04 vscode: update devcontainer.json
2023-06-04 update core module
2023-06-04 build/board: rework internal include directories
2023-06-04 board: remove unused function
2023-06-04 tests/hw: make the usage of hw controller configurable in yml config
2023-06-10 build/tests: fix incorrect paths in execute_process
2023-06-10 vscode: fix incorrect path for workspaceFolder
2023-06-10 update sysexconf module
2023-06-10 update midi module
2023-06-10 build/tests: remove redundant include
2023-06-10 build: don't include the entire modules subdir
2023-06-11 build: don't include internal board header in generated target header
2023-06-26 build: move code formatting to script for simpler usage
    otherwise bunch of character escapes are needed in cmake to make it work
2023-06-29 build: fix broken 4051 mux pin generator
2023-06-29 leds: fix invalid retrieval of blink speed
2023-06-29 tests/leds: add tests for single value control types
2023-06-29 system: allow setting 0 as led activation value
2023-09-01 build/scripts: fix muxonmux driver symbol not being generated
2023-10-12 bootloader: remove unsupported code paths
2023-10-14 build: build generated app sources for flashgen target
2023-10-14 touchscreen: don't generate icons from images (unused)
2023-10-15 remove support for viewtech touchscreens
2023-10-16 tests/leds: fix warnings
2023-10-16 build: use named arguments for gen_mcu.sh script
2023-10-26 system: add support for sending din midi clock
2023-10-26 build/gen_mcu.sh: generate only if dir doesn't exist
2023-10-28 sch: place dubfocus 16c schematics in dedicated dir
2024-02-18 build/scripts: allow arbitrary number of daisy chained max7219
2024-02-20 build: always build tests (external project)
2024-02-21 encoders: enable setting lower and upper limit for certain message types
2024-02-21 database: remove unused code
2024-02-21 database: move internal block read/write to dedicated functions
2024-02-21 system: allow disabling of forced refresh after preset change
2024-02-21 display: restore old viewtech display support
2024-03-06 ci: switch to github registry
2024-03-06 scripts/flashing/bmp: use gdb instead of arm-none-eabi-gdb
2024-03-06 ci: update actions
2024-03-06 docker-compose: consistency tweaks
2024-03-06 dockerfile: install nrf command line tools
2024-03-06 build: rework linting script
2024-03-06 vscode: install cortex debug extension
2024-03-06 app: fix include path for logger
2024-03-06 ci: save/restore cache
2024-03-13 display: shorten the MMC record string to fit on display
2024-03-13 display: rework strings and in/out text on display
2024-03-13 display: use U8X8_WITH_USER_PTR symbol for u8x8 lib
2024-03-13 display: show preset number
2024-03-13 display: remove unused variable
2024-03-14 flashgen: namespace the generated mcu header to avoid issues
2024-03-15 system: make preset change with program change in optional
2024-04-02 scripts/flashing: fix pyocd script
2024-04-03 build: regenerate and merge the flash config when application changes
2024-04-06 build: use BUILD_ALWAYS in a consistent way for external projects
    This will ensure that flashgen/sysexgen are rebuilt if they change
2024-04-06 scripts: use sudo in flashing scripts
    This avoids the need for the users to setup udev rules before flashing is possible
2024-04-08 leds: implement static control mode
    In this mode LED is on from the moment the board is powered on or
    since this mode is enabled
2024-04-15 system: set correct upper limit for button value section
2024-04-16 encoders: rename NOTE type to SINGLE_NOTE_VARIABLE_VAL for clarity
2024-04-16 encoders: add the option to send two notes depending on the direction
2024-04-16 encoders: add the option to configure two midi ids
2024-04-16 encoders: tweak the naming of position_t variable
2024-06-12 targets/mega2560_muxsh2: disable touchscreen by default due to high ram usage
2024-11-27 io: use the correct type for digital input states
2024-11-28 ci: update docker workflow
2024-11-28 style: fix formatting
2024-11-28 west: update core module
2024-11-28 devcontainer: add missing privileges
2024-12-02 messaging: add new forcedRefresh flag in event_t
2024-12-02 analog/filter: fix filtering for button message type
2024-12-02 analog/filter: lower the thresholds for digital values
2024-12-02 analog/buttons: make sure analog buttons are forcefully refreshed if requested
2024-12-02 messaging: always init messaging::event_t
2024-12-06 ci: don't edit release body on binaries upload
2024-12-08 style: update linting/formatting
2024-12-09 refactor: system-wide refactoring
    * update to latest libraries
    * rework hwa implementations for hw and tests: implementations are no longer in main.cpp but in module directories instead
    * use common/deps headers for most modules
    * use consistent init order
    * lowercase all the filenames
    * use consistent variable naming
2024-12-09 build: update west projects before the build
2024-12-10 system: rename the class to System (from Instance)
2025-11-14 leds: fix stub class typo
2025-12-17 targets: add support for dubfocus 16t
2025-12-18 buttons: add a new mmc play/stop message type
2025-12-18 misc: remove unused file
2025-12-19 devcontainer: cleanup extensions
2025-12-19 vscode: update settings
2025-12-21 scripts: add jlink flashing script
2025-12-21 vscode: add back the debug configuration and task
2025-12-23 dockerfile: install gdb-multiarch
2025-12-23 leds: rework/fix handling of global midi channel
2025-12-30 scripts: allow running pyocd without probe id
2025-12-31 targets: add indexing to dubfocus16t
2025-12-31 ci: avoid running some workflows on tag
2026-04-01 build: switch to using docker image from zenv repo
2026-04-01 style: update formatting
2026-04-01 style: use static inline where possible
2026-04-08 move sch to root dir
2026-04-09 initial db port
2026-04-09 db port
2026-05-03 refactor: port the entire codebase to zephyr rtos
2026-05-03 refactor: completely revamp emueeprom
2026-05-03 boards: add support for nucleo f767zi
2026-05-03 dts: use common dts definition for usb midi
2026-05-03 build: centralize dts/config parsing
2026-05-03 boards: add support for nucleo f446ze
2026-05-03 refactor: use proper namespacing
2026-05-03 ci: fix ordering
2026-05-03 build: drop some targets from bulk testing/linting
2026-05-03 boards: add support for nrf5340dk
2026-05-07 analog: scan only enabled inputs
2026-05-07 analog: use std::optional for sample reading
2026-05-09 midi: don't send data to usb if not ready
2026-05-12 refactor/feature: implement network/osc capabilities
2026-05-12 refactor: buttons -> switches, leds -> outputs
2026-05-13 network: various improvements
2026-05-14 boards: enable eth on nucleo h7
2026-05-14 style: resolve lint issues
2026-05-14 refactor: isolate mcu specific apis into its own module
2026-05-15 ci: use free space action
2026-05-15 system: simplify skipping of sections in backup
2026-05-15 ci: drop ccache
2026-05-15 refactor: make all includes relative to app/
2026-05-15 misc: formatting
2026-05-16 refactor: isolate hwas into dedicated dirs/libs
2026-05-16 boards: disable usb on nucleo h7/f7
2026-05-16 refactor: isolate builders into dedicated dirs
2026-05-16 analog: fix stub builder
2026-05-18 refactor: make app signaling fully async
    * route signal delivery through the async dispatcher
    * move WebConfig TX/component-info work out of producer callbacks
    * add session IDs so stale WebConfig traffic cannot affect active clients
2026-05-19 refactor: use symbols from app instead of parsing dts in tests
2026-05-19 ci: run lint
2026-05-19 midi: make ble service files part of hwa/hw cmake lib
2026-05-19 refactor: make instances consistently public in test builders
2026-05-19 tests: add missing kconfig options for system test
2026-05-19 tests: add missing module for system test
2026-05-21 usb: increase midi tx queue size
2026-05-21 firmware: increase system workqueue stack size
2026-05-21 boards: add support for wesp32 and olimex esp32 poe boards
2026-05-22 refactor: cleanup bootloader and add mdns
    * use the same construction mechanisms as in firmware
    * use mdns on network targets in bootloader
2026-05-22 dfu: refactor + isolate common parts between app and bootloader
2026-05-23 refactor: use consistent cmake lib names
2026-05-23 refactor: update to latest zlibs + zenv
2026-05-23 refactor: don't import target facts for shared tests
2026-05-23 refactor: reorg/rename tests
2026-05-23 kconfig: move logging kconfig to app dir
2026-05-24 refactor: reorganize shared test headers
2026-05-27 refactor: introduce native pwm support, cleanup pinouts
2026-05-27 refactor: use level based output control
    * drop RGB LED support
    * rename brightness/blink terminology to level/pulse
    * cleanup hwa api for outputs
    * actually implement native row output matrix driver
    * cleanup touchscreen component amount in bindings
2026-05-27 refactor: instantiate mappers directly in io handlers
2026-05-27 misc: cleanup schematics
2026-05-31 refactor: revamp i2c subsystem + implement support for various sensors
2026-06-01 refactor: move hardware linkage into modules
    * move firmware and bootloader hardware library ownership into module CMake files
    * fix WebUSB stub selection for bootloader targets without USB DFU
    * add shared Kconfig.common
2026-06-01 refactor: use opendeck::firmware namespace in fw sources
2026-06-01 refactor: rework module gating depending on target support
    * drop ifdefs around module sources and use cmake guards instead
    * rename some modules for clarity
    * split command handling and event forwarding in websockets into dedicated modules
2026-06-01 refactor: use consistent test files naming
2026-06-01 style: fix lint issues
2026-06-01 tests: misc build fixes
2026-06-01 refactor: add read i2c api
2026-06-02 dts: use random mac address on wiznet boards
2026-06-02 sysbuild: enable target-level network.conf
2026-06-04 refactor: split shared and internal headers
2026-06-04 refactor: flush db writes during config
2026-06-04 boards: tweak partitions on esp3s3
2026-06-04 refactor: implement backpressure on usb dfu, use threaded logging
2026-06-04 i2c: compile sensors only on osc targets
2026-06-04 refactor: qualify missed namespaces
2026-06-04 osc: enable by default
2026-06-04 websockets: drop useless include
2026-06-04 boards: add support for waveshare esp32 s3 eth
2026-06-04 osc: use 4 configured dest ip addresses
2026-06-04 system: add custom req to check if staged dfu is supported
2026-06-04 refactor: drop stale ifdef guards on sources
2026-06-04 boards: add support for wiznet w5500/w6100 eth shields on metro boards
2026-06-05 dts: enable staged update on wiznet pico boards
2026-06-05 fix: use openocd as default runner for f407 discovery
2026-06-05 boards: rename discovery target to discovery_f407g
2026-06-05 mdns: add osc txt metadata
2026-06-06 dts: misc fixes
2026-06-06 build: print each target in newline when calling make with wrong target
2026-06-08 boards: enable uf2 for grand central m4
2026-06-08 i2c: fix scanning on some targets
2026-06-08 dts: tweak partition sizes on esp32
2026-06-08 refactor: add mapper layer for i2c sensors
2026-06-09 database: add missing log line
2026-06-09 dts: tweak partition sizes
2026-06-11 i2c: add support for vl53l5cx sensor
2026-06-11 i2c: remove unused filter
2026-06-11 i2c: normalize the osc sensors paths
2026-06-11 build: drop esp32 targets from bulk lint
2026-06-11 i2c: use minimal filtering on bno085
2026-06-11 refactor: update to latest zlibs
2026-06-11 tests: update system test
2026-06-11 i2c: rework filtering on bno085
2026-06-11 i2c: improve apds9960 responsiveness and add more settings
2026-06-11 add processing osc examples for sensors
2026-06-12 tests/bootloader/dfu: stop depending on generated dfu binary
2026-06-12 ci/docker: optimize and parallelize jobs
2026-06-14 boards: fix support for olimex and wesp32 boards
2026-06-15 update gitattributes
